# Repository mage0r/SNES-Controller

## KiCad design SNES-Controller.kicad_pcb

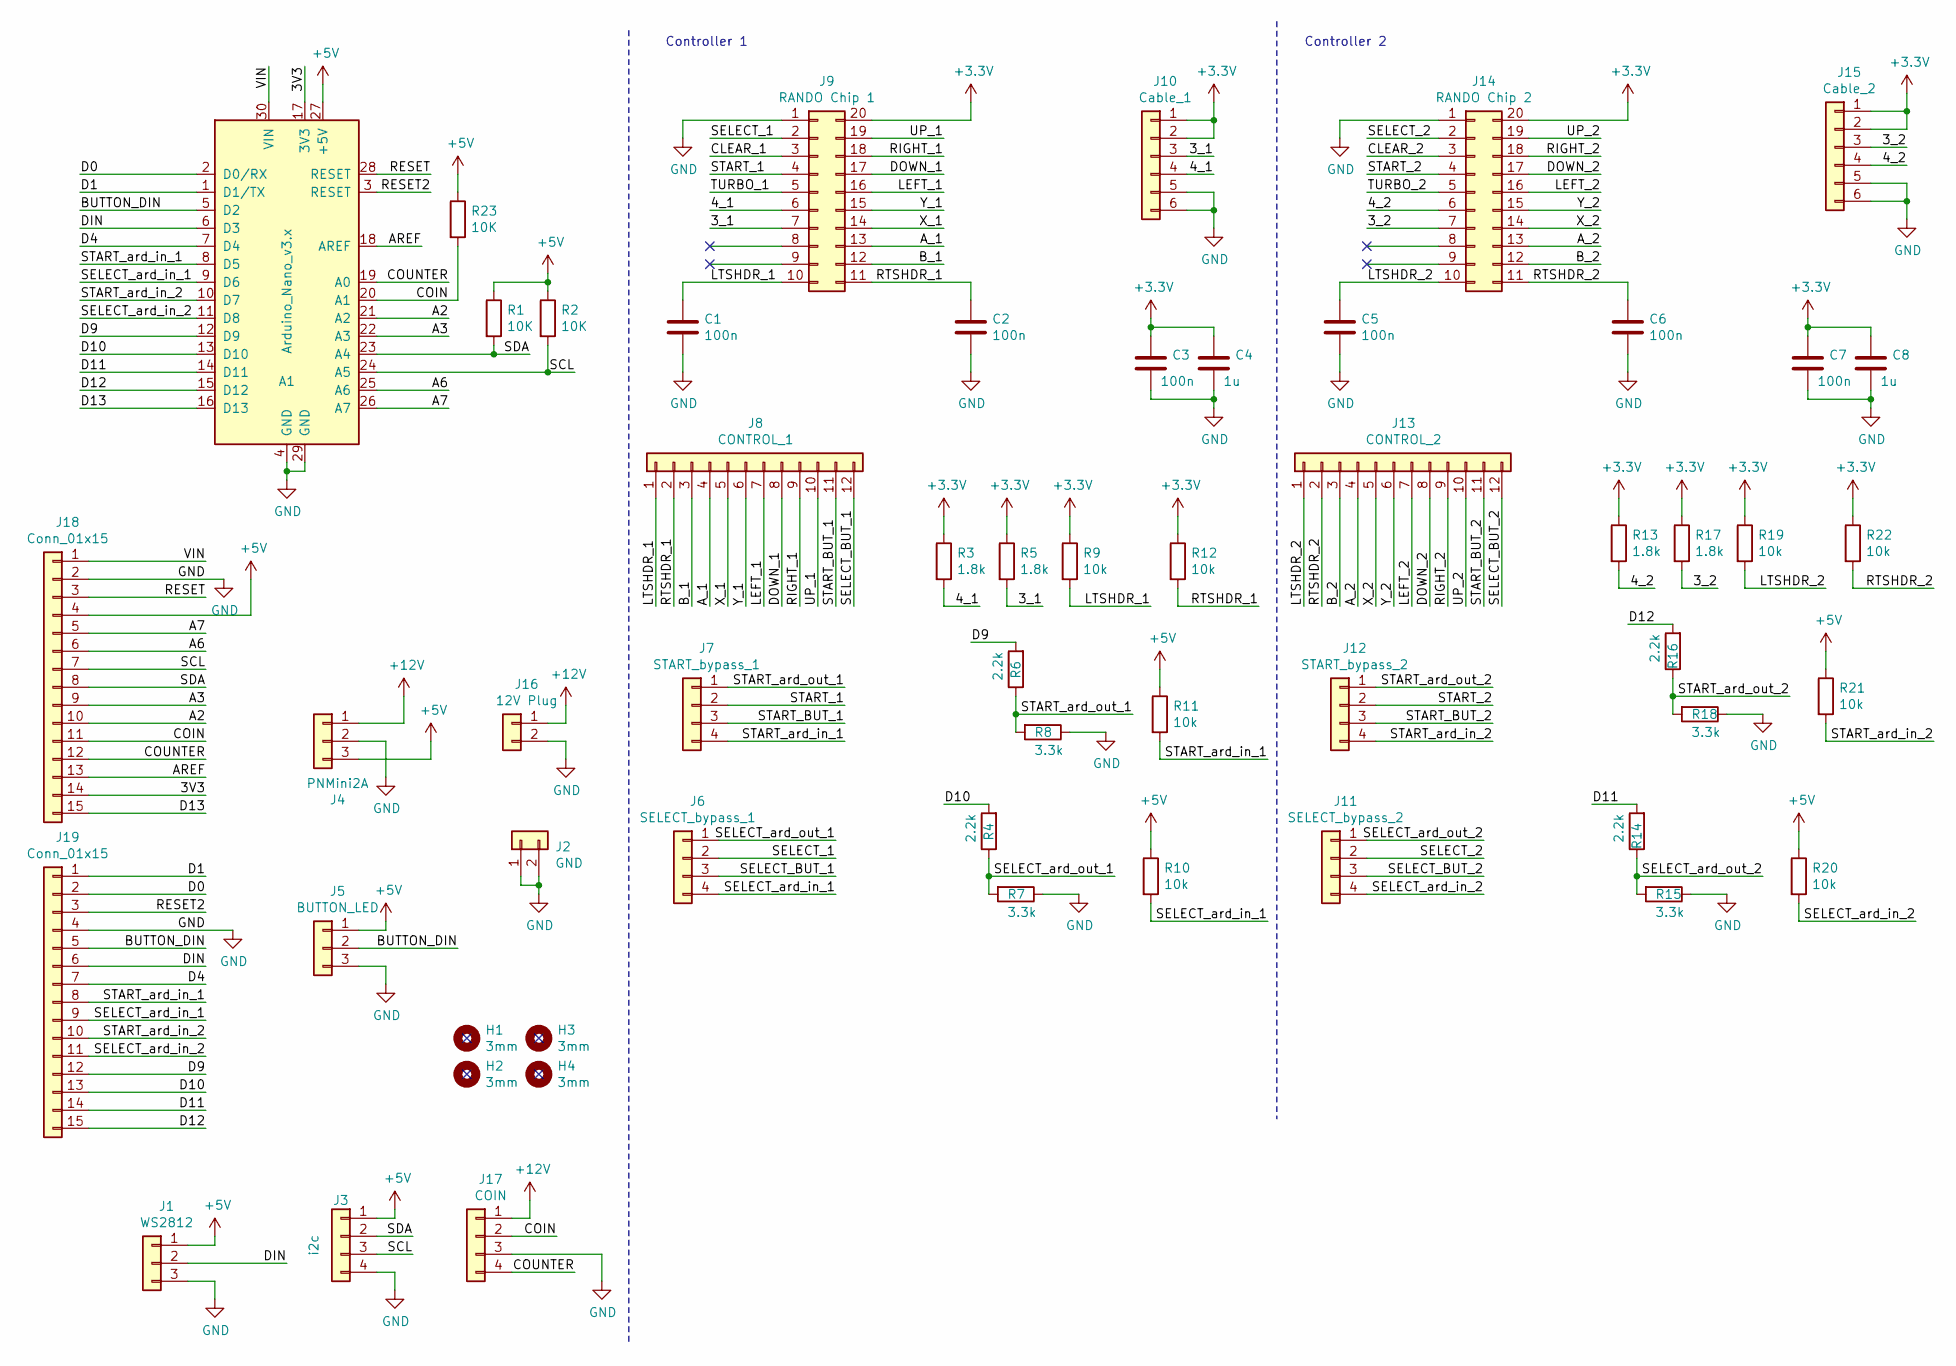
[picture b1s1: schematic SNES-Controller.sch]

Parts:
A1: Arduino_Nano_v3.x; Arduino_Nano
C1, C2, C3, C5, C6, C7: 100n; C_0603_1608Metric_Pad1.05x0.95mm_HandSolder
C4, C8: 1u; C_0603_1608Metric_Pad1.05x0.95mm_HandSolder
H1, H2, H3, H4: 3mm; MountingHole_3.2mm_M3
J1: WS2812; ScrewTerminal-Conn_3
J2: GND; ScrewTerminal-Conn_2
J3: i2c; ScrewTerminal-Conn_4
J4: PNMini2A
J5: BUTTON_LED; ScrewTerminal-Conn_3
J6: SELECT_bypass_1; PinSocket_1x04_P2.54mm_Vertical
J7: START_bypass_1; PinSocket_1x04_P2.54mm_Vertical
J8: CONTROL_1; ScrewTerminal-Conn_12
J9: RANDO Chip 1; HC2F0820SBN
J10: Cable_1; ScrewTerminal-Conn_6
J11: SELECT_bypass_2; PinSocket_1x04_P2.54mm_Vertical
J12: START_bypass_2; PinSocket_1x04_P2.54mm_Vertical
J13: CONTROL_2; ScrewTerminal-Conn_12
J14: RANDO Chip 2; HC2F0820SBN
J15: Cable_2; ScrewTerminal-Conn_6
J16: 12V Plug; ScrewTerminal-Conn_2
J17: COIN; ScrewTerminal-Conn_4
J18, J19: Conn_01x15; PinHeader_1x15_P2.54mm_Vertical
R1, R2, R23: 10K; R_0603_1608Metric_Pad1.05x0.95mm_HandSolder
R3, R5, R13, R17: 1.8k; R_0603_1608Metric_Pad1.05x0.95mm_HandSolder
R4, R6, R14, R16: 2.2k; R_0603_1608Metric_Pad1.05x0.95mm_HandSolder
R7, R8, R15, R18: 3.3k; R_0603_1608Metric_Pad1.05x0.95mm_HandSolder
R9, R10, R11, R12, R19, R20, R21, R22: 10k; R_0603_1608Metric_Pad1.05x0.95mm_HandSolder

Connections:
+3V3: C3.1, C4.1, C7.1, C8.1, J9.20, J10.1, J10.2, J14.20, J15.1, J15.2, R3.1, R5.1, R9.1, R12.1, R13.1, R17.1, R19.1, R22.1
+5V: A1.27 (+5V), J1.1, J3.1, J4.3, J5.1, J18.4, R1.1, R2.1, R10.1, R11.1, R20.1, R21.1, R23.1
+12V: J4.1, J16.1, J17.1
/3V3: A1.17 (3V3), J18.14
/3_1: J9.7, J10.3, R5.2
/3_2: J14.7, J15.3, R17.2
/4_1: J9.6, J10.4, R3.2
/4_2: J14.6, J15.4, R13.2
/A2: A1.21 (A2), J18.10
/A3: A1.22 (A3), J18.9
/A6: A1.25 (A6), J18.6
/A7: A1.26 (A7), J18.5
/AREF: A1.18 (AREF), J18.13
/A_1: J8.4, J9.13
/A_2: J13.4, J14.13
/BUTTON_DIN: A1.5 (D2), J5.2, J19.5
/B_1: J8.3, J9.12
/B_2: J13.3, J14.12
/CLEAR_1: J9.3
/CLEAR_2: J14.3
/COIN: A1.20 (A1), J17.2, J18.11, R23.2
/COUNTER: A1.19 (A0), J17.4, J18.12
/D0: A1.2 (D0/RX), J19.2
/D1: A1.1 (D1/TX), J19.1
/D4: A1.7 (D4), J19.7
/D9: A1.12 (D9), J19.12, R6.2
/D10: A1.13 (D10), J19.13, R4.2
/D11: A1.14 (D11), J19.14, R14.2
/D12: A1.15 (D12), J19.15, R16.2
/D13: A1.16 (D13), J18.15
/DIN: A1.6 (D3), J1.2, J19.6
/DOWN_1: J8.8, J9.17
/DOWN_2: J13.8, J14.17
/LEFT_1: J8.7, J9.16
/LEFT_2: J13.7, J14.16
/LTSHDR_1: C1.1, J8.1, J9.10, R9.2
/LTSHDR_2: C5.1, J13.1, J14.10, R19.2
/RESET: A1.28 (RESET), J18.3
/RESET2: A1.3 (RESET), J19.3
/RIGHT_1: J8.9, J9.18
/RIGHT_2: J13.9, J14.18
/RTSHDR_1: C2.1, J8.2, J9.11, R12.2
/RTSHDR_2: C6.1, J13.2, J14.11, R22.2
/SCL: A1.24 (A5), J3.3, J18.7, R2.2
/SDA: A1.23 (A4), J3.2, J18.8, R1.2
/SELECT_1: J6.2, J9.2
/SELECT_2: J11.2, J14.2
/SELECT_BUT_1: J6.3, J8.12
/SELECT_BUT_2: J11.3, J13.12
/SELECT_ard_in_1: A1.9 (D6), J6.4, J19.9, R10.2
/SELECT_ard_in_2: A1.11 (D8), J11.4, J19.11, R20.2
/SELECT_ard_out_1: J6.1, R4.1, R7.2
/SELECT_ard_out_2: J11.1, R14.1, R15.2
/START_1: J7.2, J9.4
/START_2: J12.2, J14.4
/START_BUT_1: J7.3, J8.11
/START_BUT_2: J12.3, J13.11
/START_ard_in_1: A1.8 (D5), J7.4, J19.8, R11.2
/START_ard_in_2: A1.10 (D7), J12.4, J19.10, R21.2
/START_ard_out_1: J7.1, R6.1, R8.2
/START_ard_out_2: J12.1, R16.1, R18.2
/TURBO_1: J9.5
/TURBO_2: J14.5
/UP_1: J8.10, J9.19
/UP_2: J13.10, J14.19
/VIN: A1.30 (VIN), J18.1
/X_1: J8.5, J9.14
/X_2: J13.5, J14.14
/Y_1: J8.6, J9.15
/Y_2: J13.6, J14.15
GND: A1.4 (GND), A1.29 (GND), C1.2, C2.2, C3.2, C4.2, C5.2, C6.2, C7.2, C8.2, J1.3, J2.1, J2.2, J3.4, J4.2, J5.3, J9.1, J10.5, J10.6, J14.1, J15.5, J15.6, J16.2, J17.3, J18.2, J19.4, R7.1, R8.1, R15.1, R18.1

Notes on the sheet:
Controller 2
Controller 1

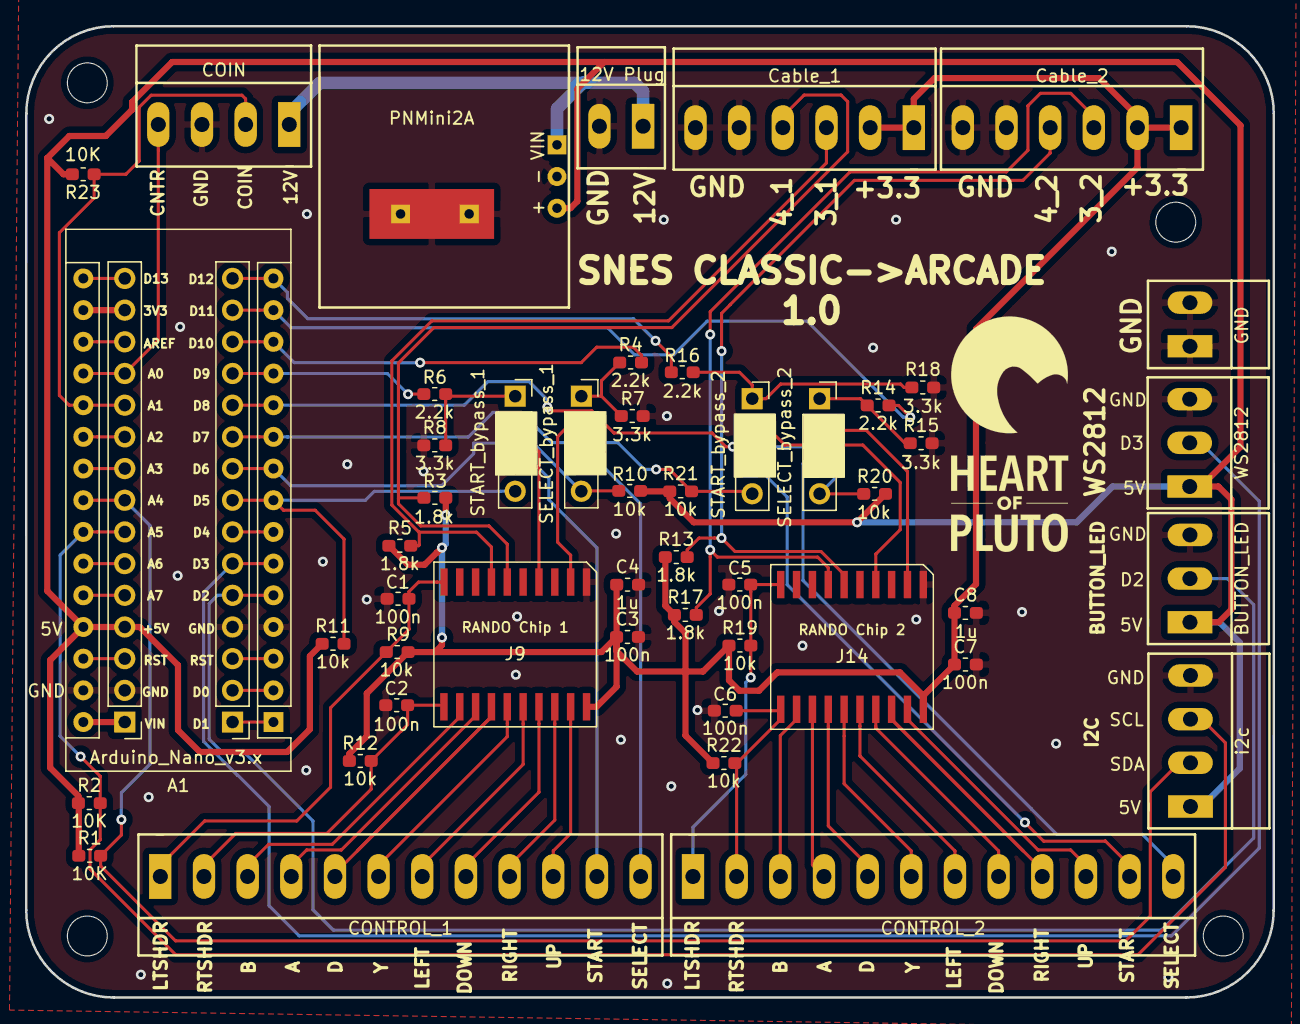
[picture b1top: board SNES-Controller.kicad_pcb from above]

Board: 2 copper layers, 100.0 x 77.9 mm, 55 parts (0 on the bottom side), 67 nets.

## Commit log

2021-01-27 :boom::camel: Added .gitattributes & .gitignore files
2021-01-27 Initial push
